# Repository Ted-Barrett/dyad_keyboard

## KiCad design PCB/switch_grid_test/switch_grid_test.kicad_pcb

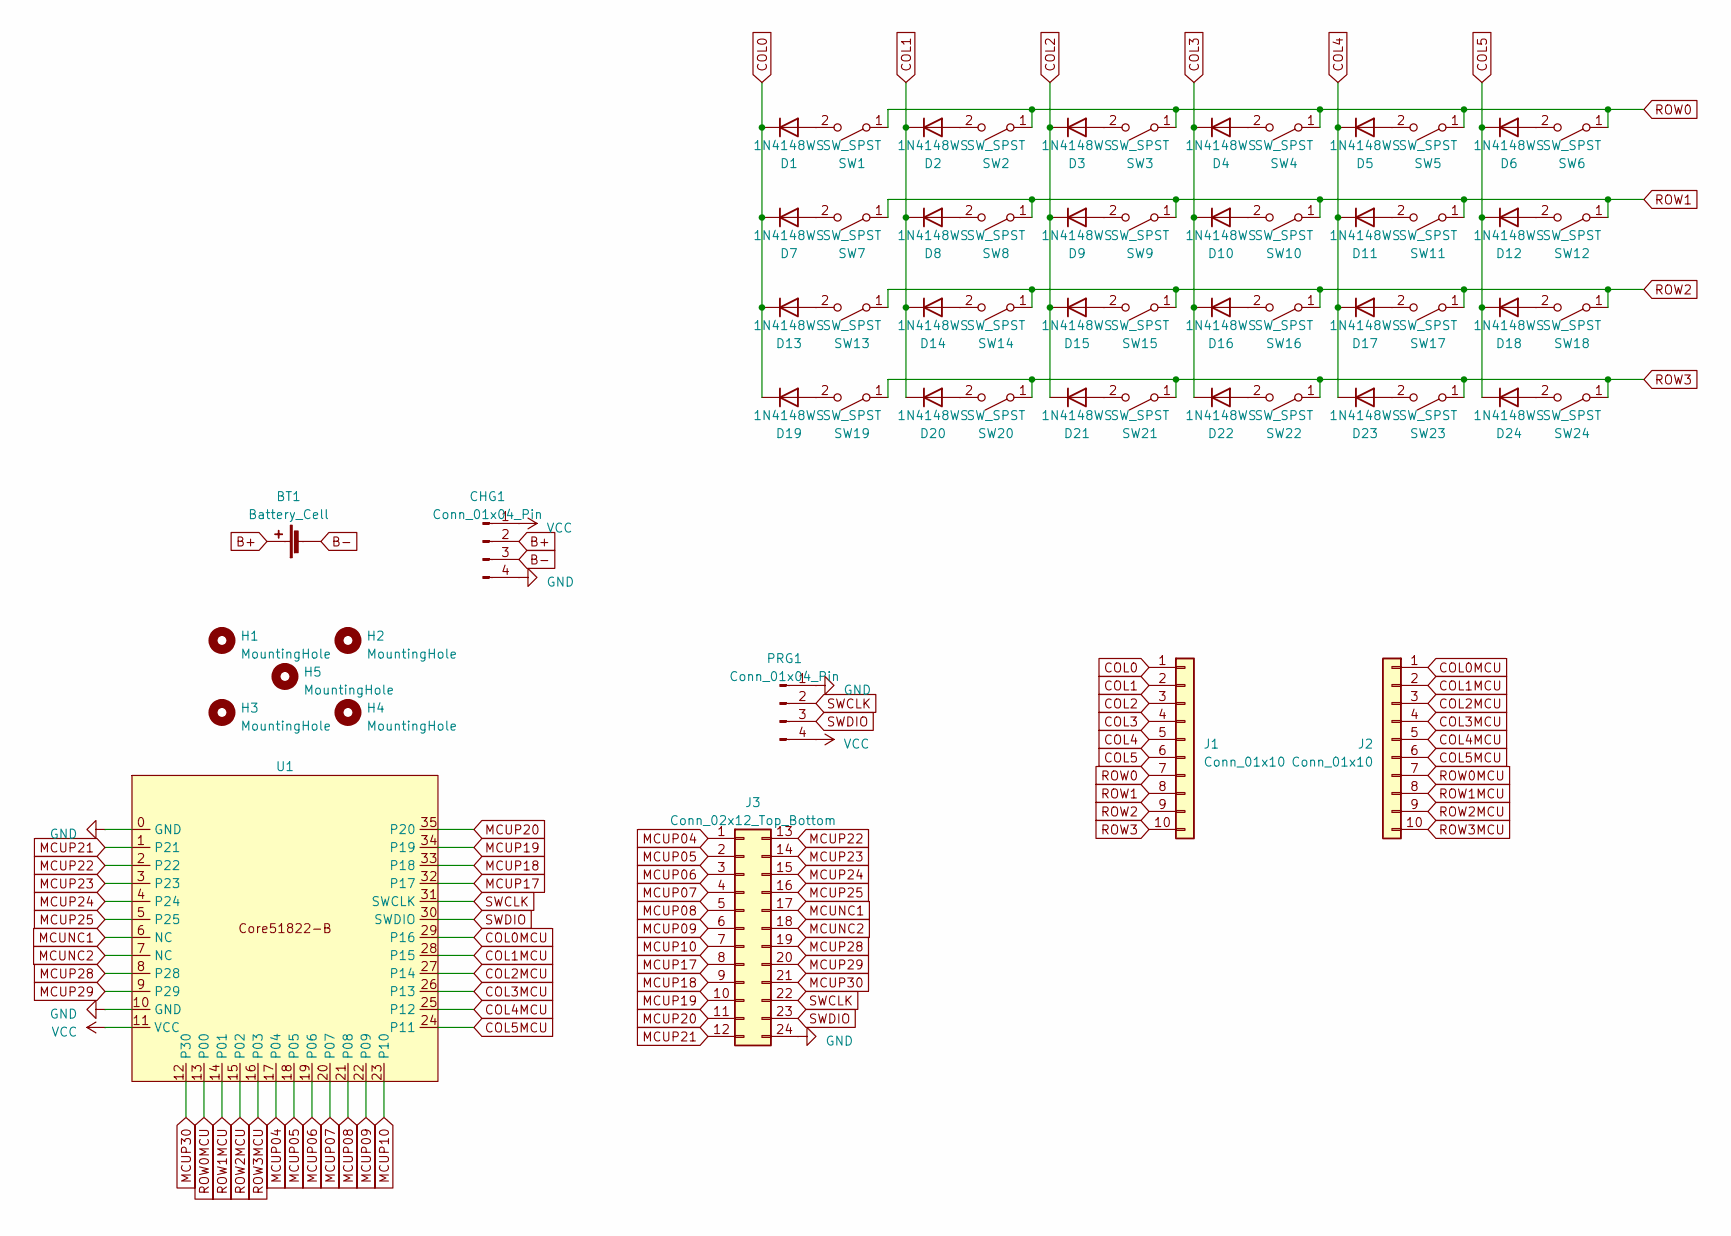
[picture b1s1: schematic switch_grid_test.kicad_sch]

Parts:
BT1: Battery_Cell; MY-2032-31
CHG1: Conn_01x04_Pin; PinHeader_1x04_P2.54mm_Vertical
D1, D2, D3, D4, D5, D6, D7, D8, D9, D10, D11, D12, D13, D14, D15, D16, D17, D18, D19, D20, D21, D22, D23, D24: 1N4148WS; D_SOD-323
H1, H2, H3, H4, H5: MountingHole; MountingHole_2mm
J1, J2: Conn_01x10; PinSocket_1x10_P2.54mm_Vertical
J3: Conn_02x12_Top_Bottom; PinSocket_2x12_P2.54mm_Vertical
PRG1: Conn_01x04_Pin; PinHeader_1x04_P2.54mm_Vertical
SW1, SW2, SW3, SW4, SW5, SW6, SW7, SW8, SW9, SW10, SW11, SW12, SW13, SW14, SW15, SW16, SW17, SW18, SW19, SW20, SW21, SW22, SW23, SW24: SW_SPST; Kailh_socket_MX
U1: core51822-b

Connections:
B+: BT1.1 (+), CHG1.2
B-: BT1.2 (-), CHG1.3
COL0: D1.1 (K), D7.1 (K), D13.1 (K), D19.1 (K), J1.1
COL0MCU: J2.1, U1.29 (P16)
COL1: D2.1 (K), D8.1 (K), D14.1 (K), D20.1 (K), J1.2
COL1MCU: J2.2, U1.28 (P15)
COL2: D3.1 (K), D9.1 (K), D15.1 (K), D21.1 (K), J1.3
COL2MCU: J2.3, U1.27 (P14)
COL3: D4.1 (K), D10.1 (K), D16.1 (K), D22.1 (K), J1.4
COL3MCU: J2.4, U1.26 (P13)
COL4: D5.1 (K), D11.1 (K), D17.1 (K), D23.1 (K), J1.5
COL4MCU: J2.5, U1.25 (P12)
COL5: D6.1 (K), D12.1 (K), D18.1 (K), D24.1 (K), J1.6
COL5MCU: J2.6, U1.24 (P11)
GND: CHG1.4, J3.24, PRG1.1, U1.0 (GND), U1.10 (GND)
MCUNC1: J3.17, U1.6 (NC)
MCUNC2: J3.18, U1.7 (NC)
MCUP04: J3.1, U1.17 (P04)
MCUP05: J3.2, U1.18 (P05)
MCUP06: J3.3, U1.19 (P06)
MCUP07: J3.4, U1.20 (P07)
MCUP08: J3.5, U1.21 (P08)
MCUP09: J3.6, U1.22 (P09)
MCUP10: J3.7, U1.23 (P10)
MCUP17: J3.8, U1.32 (P17)
MCUP18: J3.9, U1.33 (P18)
MCUP19: J3.10, U1.34 (P19)
MCUP20: J3.11, U1.35 (P20)
MCUP21: J3.12, U1.1 (P21)
MCUP22: J3.13, U1.2 (P22)
MCUP23: J3.14, U1.3 (P23)
MCUP24: J3.15, U1.4 (P24)
MCUP25: J3.16, U1.5 (P25)
MCUP28: J3.19, U1.8 (P28)
MCUP29: J3.20, U1.9 (P29)
MCUP30: J3.21, U1.12 (P30)
unnamed: D1.2 (A), SW1.2 (B)
unnamed: D2.2 (A), SW2.2 (B)
unnamed: D3.2 (A), SW3.2 (B)
unnamed: D4.2 (A), SW4.2 (B)
unnamed: D5.2 (A), SW5.2 (B)
unnamed: D6.2 (A), SW6.2 (B)
unnamed: D7.2 (A), SW7.2 (B)
unnamed: D8.2 (A), SW8.2 (B)
unnamed: D9.2 (A), SW9.2 (B)
unnamed: D10.2 (A), SW10.2 (B)
unnamed: D11.2 (A), SW11.2 (B)
unnamed: D12.2 (A), SW12.2 (B)
unnamed: D13.2 (A), SW13.2 (B)
unnamed: D14.2 (A), SW14.2 (B)
unnamed: D15.2 (A), SW15.2 (B)
unnamed: D16.2 (A), SW16.2 (B)
unnamed: D17.2 (A), SW17.2 (B)
unnamed: D18.2 (A), SW18.2 (B)
unnamed: D19.2 (A), SW19.2 (B)
unnamed: D20.2 (A), SW20.2 (B)
unnamed: D21.2 (A), SW21.2 (B)
unnamed: D22.2 (A), SW22.2 (B)
unnamed: D23.2 (A), SW23.2 (B)
unnamed: D24.2 (A), SW24.2 (B)
ROW0: J1.7, SW1.1 (A), SW2.1 (A), SW3.1 (A), SW4.1 (A), SW5.1 (A), SW6.1 (A)
ROW0MCU: J2.7, U1.13 (P00)
ROW1: J1.8, SW7.1 (A), SW8.1 (A), SW9.1 (A), SW10.1 (A), SW11.1 (A), SW12.1 (A)
ROW1MCU: J2.8, U1.14 (P01)
ROW2: J1.9, SW13.1 (A), SW14.1 (A), SW15.1 (A), SW16.1 (A), SW17.1 (A), SW18.1 (A)
ROW2MCU: J2.9, U1.15 (P02)
ROW3: J1.10, SW19.1 (A), SW20.1 (A), SW21.1 (A), SW22.1 (A), SW23.1 (A), SW24.1 (A)
ROW3MCU: J2.10, U1.16 (P03)
SWCLK: J3.22, PRG1.2, U1.31 (SWCLK)
SWDIO: J3.23, PRG1.3, U1.30 (SWDIO)
VCC: CHG1.1, PRG1.4, U1.11 (VCC)

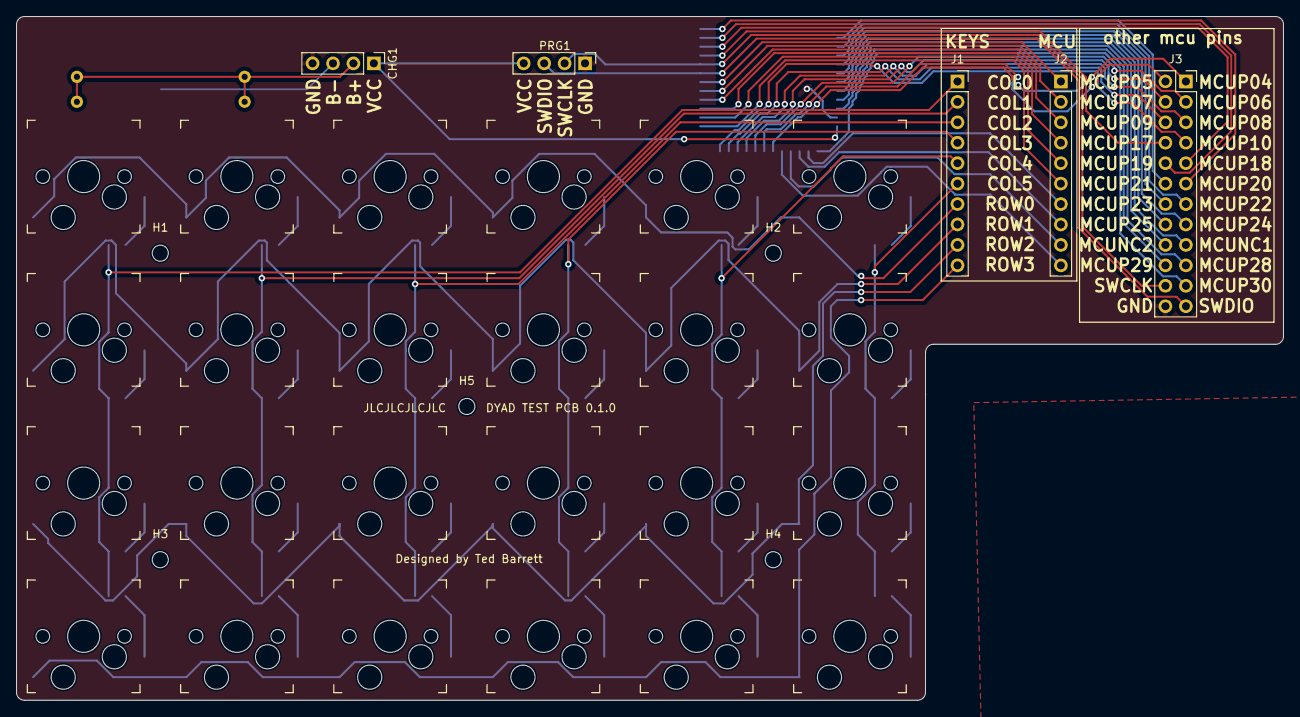
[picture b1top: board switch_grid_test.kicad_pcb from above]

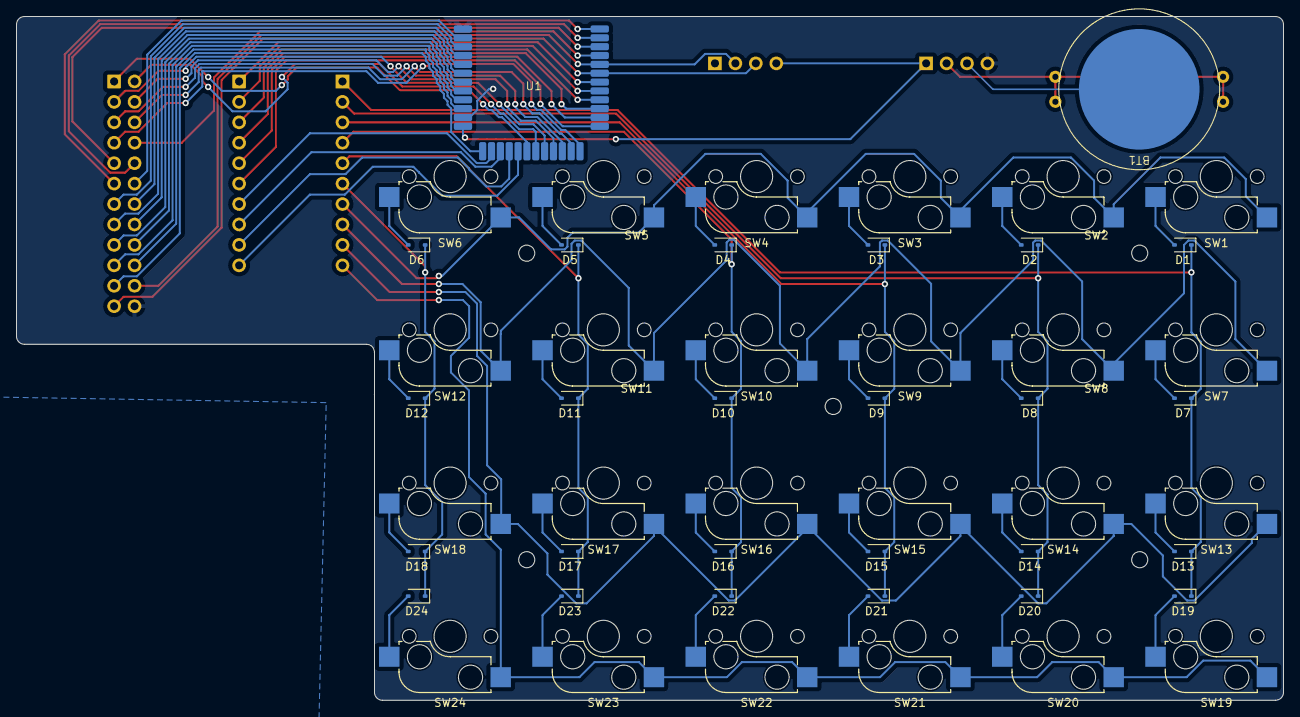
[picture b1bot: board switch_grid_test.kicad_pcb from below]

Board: 2 copper layers, 157.5 x 85.0 mm, 60 parts (26 on the bottom side), 71 nets.

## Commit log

2023-03-12 create kicad project
2023-03-12 add diodes
2023-03-12 added mounting holes
2023-03-18 update pcb and schematic
2023-05-30 stuff
2023-05-30 libraries
2023-05-30 make libraries local
